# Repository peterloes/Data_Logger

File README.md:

# Next generation of data logger for varied range support of sensors.

A standalone platform to get environmental impact around organisms (animals).
Enable long-term observations of different selectable sensors (I2C Interfaces).
Two pulse counters are included to get lightbarrier activity.

Authors: Loës P., Kempenaers B.(2021) 

## Main advantages against other data logger:

- Available sensors can be freely combined as required.(Firmware adaption)
- Daily regular synchronisation from date and time with DCF77 radio clock receiver.(Firmware adaption)
- Long battery life with lithium battery. (max.17V)
- SD Card includes configuration file.
- Activation times for sensors (x5) to collect data.

## Hardware Design (first draft) supported:

The following firmware is not reviewed.

- Sensirion: Humidity and Temperature Sensor SHT3x-DIS
- Sensirion: CO₂, Humidity and Temperature Sensor SCD30
- Vishay: Fully Integrated Proximity and Ambient Light Sensor with Infrared Emitter VCNL4040
- Pulse Counter     	 

Board Dimensions: 80mm x 60mm

Raw data on SD Card:

https://github.com/peterloes/Data_Logger/blob/main/Getting_Started_Tutorial/4_rawdata_BOX0999.TXT

Configuration data on SD Card:

https://github.com/peterloes/Data_Logger/blob/main/Software/CONFIG.TXT

Schematics:

https://github.com/peterloes/Data_Logger/blob/main/Schematics/Logger.sch.pdf

Housing:

https://github.com/peterloes/Data_Logger/blob/main/Getting_Started_Tutorial/11_Electronic_housing.jpg

## Hyperterminal Screens

Shows SHT31X-D (0x45) and SHT31X-D (0x45)

https://github.com/peterloes/Data_Logger/blob/main/Getting_Started_Tutorial/3_Hyperterminal_3.jpg

https://github.com/peterloes/Data_Logger/blob/main/Getting_Started_Tutorial/3_Hyperterminal_4.jpg

In operation with Interval (configuration.txt) : 3,2V@0,54mA

Shows Vishay VCNL4040 (0x60) and SHT31X-D (0x45)

https://github.com/peterloes/Data_Logger/blob/main/Getting_Started_Tutorial/3_Hyperterminal_5.jpg

Shows Vishay VCNL4040 (0x60) and Sensirion SCD30 CO2 (0x61)

https://github.com/peterloes/Data_Logger/blob/main/Getting_Started_Tutorial/3_Hyperterminal_6.jpg

## Board Power

 - Lithium battery  17V/300mA(maximum) e.g. 12,8V 7,5Ah 96Wh 
 - LS14250 Primary Lithium-Thionyl chloride    3.6V/1200mAh 

Sensors can powered by VBATT_1(3.3V), VBATT_2(3V):

 - Sensirion: Humidity and Temperature Sensor SHT3x-DIS:        600µA@3,3V

 - Sensirion: CO₂, Humidity and Temperature Sensor SCD30:     max.75mA@3,3V 

 - Vishay: Proximity Sensor and Ambient Light Sensor VCNL 4040: 300µA@2,5V

   Similar Software(SensorMon.c): https://github.com/peterloes/HRD_SENSOR

Optional components:

https://github.com/peterloes/Clock_receiver_RFID-MS_MOMO_TAMDL

https://github.com/peterloes/Booter_RFID-MS_MOMO_TAMDL

Outlook:

The Data Logger can feature two arrays with different sensors over 25 meters. (sensor-array x 2)

C is the Greenest Programming Language

To achieve its power and energy-efficiency features, EFM32 products utilize ultralow active and idle power,
fast wakeup and processing times, and most important, the ability to intelligently interact with peripherals
and sensors autonomously without waking up the CPU and consuming more power.

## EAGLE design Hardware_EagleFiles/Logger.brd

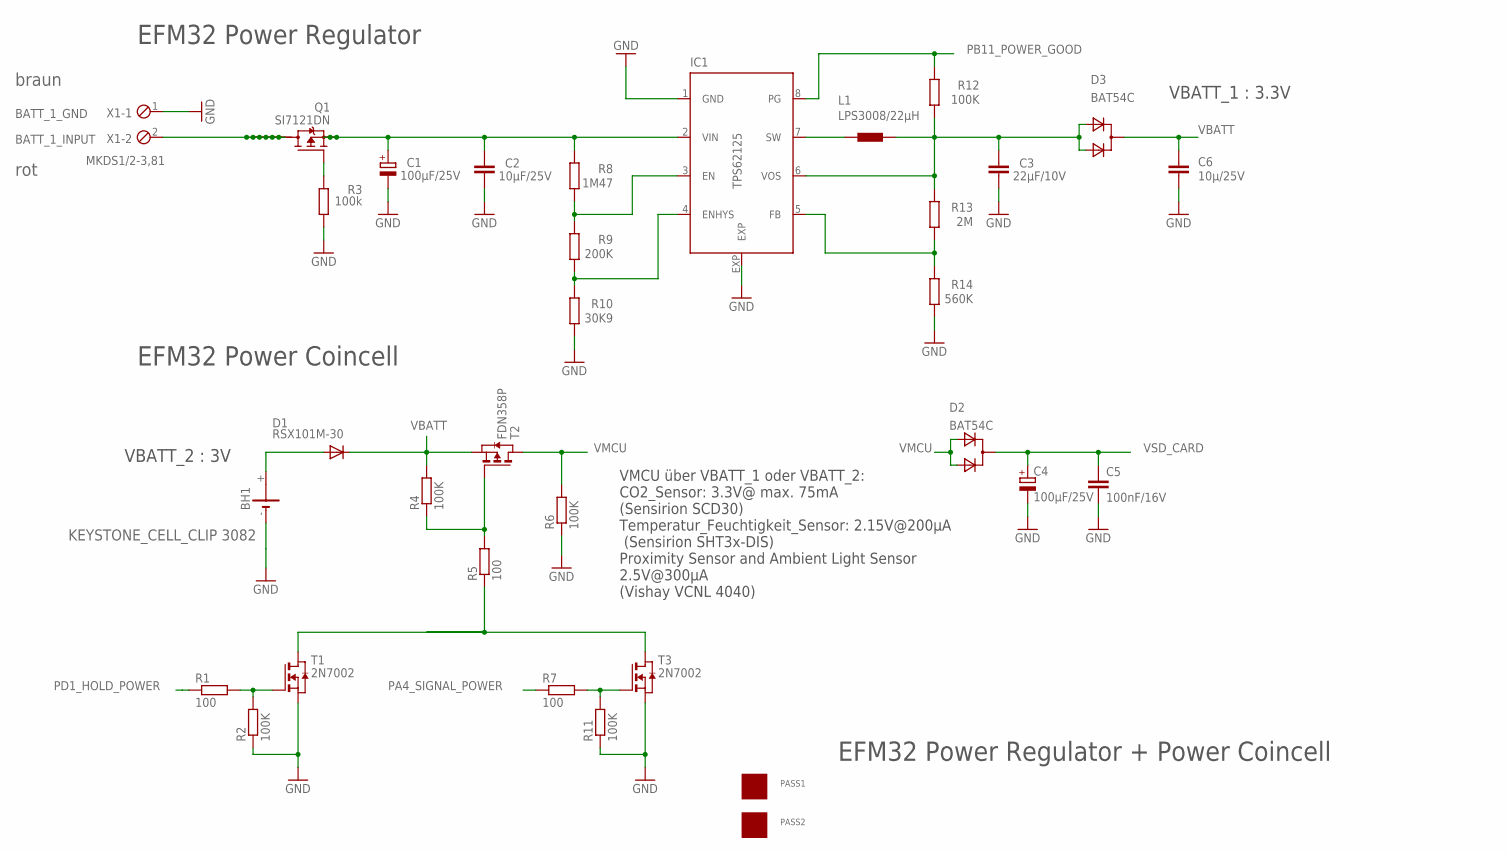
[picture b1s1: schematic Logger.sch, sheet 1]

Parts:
BH1: KEYSTONE_CELL_CLIP 3082; 3082
C1, C4: 100µF/25V; PANASONIC_E
C2: 10µF/25V; C1206
C3: 22µF/10V; C0603
C5: 100nF/16V; C0805
C6: 10µ/25V; C1206
D1: RSX101M-30; SOD123
D2, D3: BAT54C; SOT-23$1
IC1: TPS62125; DSG_PWSO-N8_EXP
L1: LPS3008/22µH; LPS3008
PASS1, PASS2: ROUND_1MM1.5; ROUND2_1.5MM
Q1: SI7121DN; TRANSISTOR-FET_1212-8S
R1, R5, R7: 100; R0805
R2, R4, R6, R11, R12: 100K; R0805
R3: 100k; R0805
R8: 1M47; R0805
R9: 200K; R0805
R10: 30K9; R0805
R13: 2M; R0805
R14: 560K; R0805
T1, T3: 2N7002; SOT-23
T2: FDN358P; ZETEX_SOT-23
X1: MKDS1/2-3,81; 2POL381

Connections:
1: C3.1, D3.2 (A1), D3.3 (A2), IC1.6 (VOS), L1.2, R12.1, R13.2
BATT_INPUT: C1.+, C2.1, IC1.2 (VIN), Q1.1 (S), Q1.2 (S), Q1.3 (S), R8.2
GND: BH1.-, C1.-, C2.2, C3.2, C4.-, C5.2, C6.1, IC1.1 (GND), IC1.EXP, R2.1, R3.1, R6.1, R10.1, R11.1, R14.1, T1.2 (S), T3.2 (S), X1.1; also elsewhere on the board
unnamed: R1.2, R2.2, T1.3 (G)
unnamed: IC1.3 (EN), R8.1, R9.2
unnamed: IC1.4 (ENHYS), R9.1, R10.2
unnamed: IC1.7 (SW), L1.1
unnamed: BH1.+, D1.A
unnamed: Q1.4 (G), R3.2
unnamed: R4.1, R5.2, T2.3 (G)
unnamed: R7.2, R11.2, T3.3 (G)
unnamed: R5.1, T1.1 (D), T3.1 (D)
unnamed: IC1.5 (FB), R13.1, R14.2
PA4_SIGNAL_POWER: R7.1; also elsewhere on the board
PB11_POWER_GOOD: IC1.8 (PG), R12.2; also elsewhere on the board
PD1_HOLD_POWER: R1.1; also elsewhere on the board
VBATT: C6.2, D1.C, D3.1 (C), R4.2, T2.2 (S); also elsewhere on the board
VMCU: D2.2 (A1), D2.3 (A2), R6.2, T2.1 (D); also elsewhere on the board
VSD_CARD: C4.+, C5.1, D2.1 (C); also elsewhere on the board
_: Q1.5 (D), Q1.6 (D), Q1.7 (D), Q1.8 (D), Q1.9 (D), Q1.10 (D), Q1.11 (D), X1.2

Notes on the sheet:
BATT_1_GND
BATT_1_INPUT
EFM32 Power Regulator + Power Coincell
EFM32 Power Regulator
VBATT_1 : 3.3V
braun
rot
EFM32 Power Coincell
VBATT_2 : 3V
VMCU über VBATT_1 oder VBATT_2: CO2_Sensor: 3.3V@ max. 75mA (Sensirion SCD30) Temperatur_Feuchtigkeit_Sensor: 2.15V@200µA (Sensirion SHT3x-DIS) Proximity Sensor and Ambient Light Sensor 2.5V@300µA (Vishay VCNL 4040)

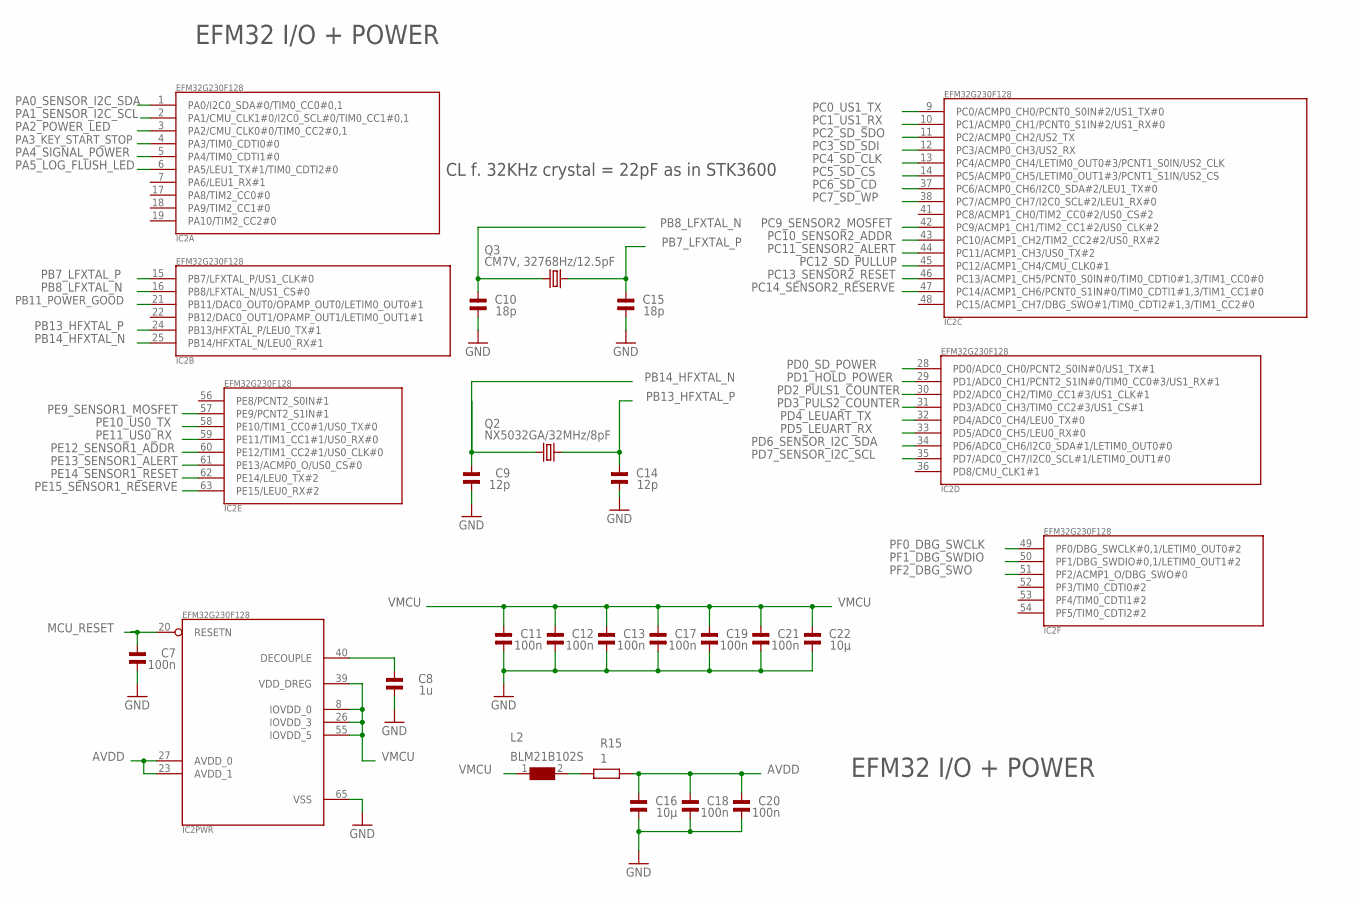
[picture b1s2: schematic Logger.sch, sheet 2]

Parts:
C7, C11, C12, C13, C17, C18, C19, C20, C21: 100n; 0805
C8: 1u; 0805
C9, C14: 12p; 0805
C10, C15: 18p; 0805
C16, C22: 10µ; 0805
IC2: EFM32G230F128; QFN64
L2: BLM21B102S; 0805
Q2: NX5032GA/32MHz/8pF; CRYSTAL2P5.0X3.2
Q3: CM7V, 32768Hz/12.5pF; CRYSTAL2P3.2X1.5
R15: 1; R0805

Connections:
AVDD: C16.2, C18.2, C20.2, IC2.23 (AVDD_1), IC2.27 (AVDD_0), R15.2
GND: C7.1, C8.1, C9.1, C10.1, C11.1, C12.1, C13.1, C14.1, C15.1, C16.1, C17.1, C18.1, C19.1, C20.1, C21.1, C22.1, IC2.65 (VSS); also elsewhere on the board
MCU_RESET: C7.2, IC2.20 (RESETN); also elsewhere on the board
unnamed: L2.2, R15.1
unnamed: C8.2, IC2.40 (DECOUPLE)
PA0_SENSOR_I2C_SDA: IC2.1 (PA0/I2C0_SDA#0/TIM0_CC0#0,1); also elsewhere on the board
PA1_SENSOR_I2C_SCL: IC2.2 (PA1/CMU_CLK1#0/I2C0_SCL#0/TIM0_CC1#0,1); also elsewhere on the board
PA2_POWER_LED: IC2.3 (PA2/CMU_CLK0#0/TIM0_CC2#0,1); also elsewhere on the board
PA3_KEY_START_STOP: IC2.4 (PA3/TIM0_CDTI0#0); also elsewhere on the board
PA4_SIGNAL_POWER: IC2.5 (PA4/TIM0_CDTI1#0); also elsewhere on the board
PA5_LOG_FLUSH_LED: IC2.6 (PA5/LEU1_TX#1/TIM0_CDTI2#0); also elsewhere on the board
PB7_LFXTAL_P: C15.2, IC2.15 (PB7/LFXTAL_P/US1_CLK#0), Q3.2
PB8_LFXTAL_N: C10.2, IC2.16 (PB8/LFXTAL_N/US1_CS#0), Q3.1
PB11_POWER_GOOD: IC2.21 (PB11/DAC0_OUT0/OPAMP_OUT0/LETIM0_OUT0#1); also elsewhere on the board
PB13_HFXTAL_P: C14.2, IC2.24 (PB13/HFXTAL_P/LEU0_TX#1), Q2.2
PB14_HFXTAL_N: C9.2, IC2.25 (PB14/HFXTAL_N/LEU0_RX#1), Q2.1
PC0_US1_TX: IC2.9 (PC0/ACMP0_CH0/PCNT0_S0IN#2/US1_TX#0); also elsewhere on the board
PC1_US1_RX: IC2.10 (PC1/ACMP0_CH1/PCNT0_S1IN#2/US1_RX#0); also elsewhere on the board
PC2_SD_SDO: IC2.11 (PC2/ACMP0_CH2/US2_TX); also elsewhere on the board
PC3_SD_SDI: IC2.12 (PC3/ACMP0_CH3/US2_RX); also elsewhere on the board
PC4_SD_CLK: IC2.13 (PC4/ACMP0_CH4/LETIM0_OUT0#3/PCNT1_S0IN/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); also elsewhere on the board
PC5_SD_CS: IC2.14 (PC5/ACMP0_CH5/LETIM0_OUT1#3/PCNT1_S1IN/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); also elsewhere on the board
PC6_SD_CD: IC2.37 (PC6/ACMP0_CH6/I2C0_SDA#2/LEU1_TX#0); also elsewhere on the board
PC7_SD_WP: IC2.38 (PC7/ACMP0_CH7/I2C0_SCL#2/LEU1_RX#0); also elsewhere on the board
PC9_SENSOR2_MOSFET: IC2.42 (PC9/ACMP1_CH1/TIM2_CC1#2/US0_CLK#2); also elsewhere on the board
PC10_SENSOR2_ADDR: IC2.43 (PC10/ACMP1_CH2/TIM2_CC2#2/US0_RX#2); also elsewhere on the board
PC11_SENSOR2_ALERT: IC2.44 (PC11/ACMP1_CH3/US0_TX#2); also elsewhere on the board
PC12_SD_PULLUP: IC2.45 (PC12/ACMP1_CH4/CMU_CLK0#1); also elsewhere on the board
PC13_SENSOR2_RESET: IC2.46 (PC13/ACMP1_CH5/PCNT0_S0IN#0/TIM0_CDTI0#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); also elsewhere on the board
PC14_SENSOR2_RESERVE: IC2.47 (PC14/ACMP1_CH6/PCNT0_S1IN#0/TIM0_CDTI1#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); also elsewhere on the board
PD0_SD_POWER: IC2.28 (PD0/ADC0_CH0/PCNT2_S0IN#0/US1_TX#1); also elsewhere on the board
PD1_HOLD_POWER: IC2.29 (PD1/ADC0_CH1/PCNT2_S1IN#0/TIM0_CC0#3/US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); also elsewhere on the board
PD2_PULS1_COUNTER: IC2.30 (PD2/ADC0_CH2/TIM0_CC1#3/US1_CLK#1); also elsewhere on the board
PD3_PULS2_COUNTER: IC2.31 (PD3/ADC0_CH3/TIM0_CC2#3/US1_CS#1); also elsewhere on the board
PD4_LEUART_TX: IC2.32 (PD4/ADC0_CH4/LEU0_TX#0); also elsewhere on the board
PD5_LEUART_RX: IC2.33 (PD5/ADC0_CH5/LEU0_RX#0); also elsewhere on the board
PD6_SENSOR_I2C_SDA: IC2.34 (PD6/ADC0_CH6/I2C0_SDA#1/LETIM0_OUT0#0); also elsewhere on the board
PD7_SENSOR_I2C_SCL: IC2.35 (PD7/ADC0_CH7/I2C0_SCL#1/LETIM0_OUT1#0); also elsewhere on the board
PE9_SENSOR1_MOSFET: IC2.57 (PE9/PCNT2_S1IN#1); also elsewhere on the board
PE10_US0_TX: IC2.58 (PE10/TIM1_CC0#1/US0_TX#0); also elsewhere on the board
PE11_US0_RX: IC2.59 (PE11/TIM1_CC1#1/US0_RX#0); also elsewhere on the board
PE12_SENSOR1_ADDR: IC2.60 (PE12/TIM1_CC2#1/US0_CLK#0); also elsewhere on the board
PE13_SENSOR1_ALERT: IC2.61 (PE13/ACMP0_O/US0_CS#0); also elsewhere on the board
PE14_SENSOR1_RESET: IC2.62 (PE14/LEU0_TX#2); also elsewhere on the board
PE15_SENSOR1_RESERVE: IC2.63 (PE15/LEU0_RX#2); also elsewhere on the board
PF0_DBG_SWCLK: IC2.49 (PF0/DBG_SWCLK#0,1/LETIM0_OUT0#2); also elsewhere on the board
PF1_DBG_SWDIO: IC2.50 (PF1/DBG_SWDIO#0,1/LETIM0_OUT1#2); also elsewhere on the board
PF2_DBG_SWO: IC2.51 (PF2/ACMP1_O/DBG_SWO#0); also elsewhere on the board
VMCU: C11.2, C12.2, C13.2, C17.2, C19.2, C21.2, C22.2, IC2.8 (IOVDD_0), IC2.26 (IOVDD_3), IC2.39 (VDD_DREG), IC2.55 (IOVDD_5), L2.1; also elsewhere on the board

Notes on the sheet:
EFM32 I/O + POWER
CL f. 32KHz crystal = 22pF as in STK3600

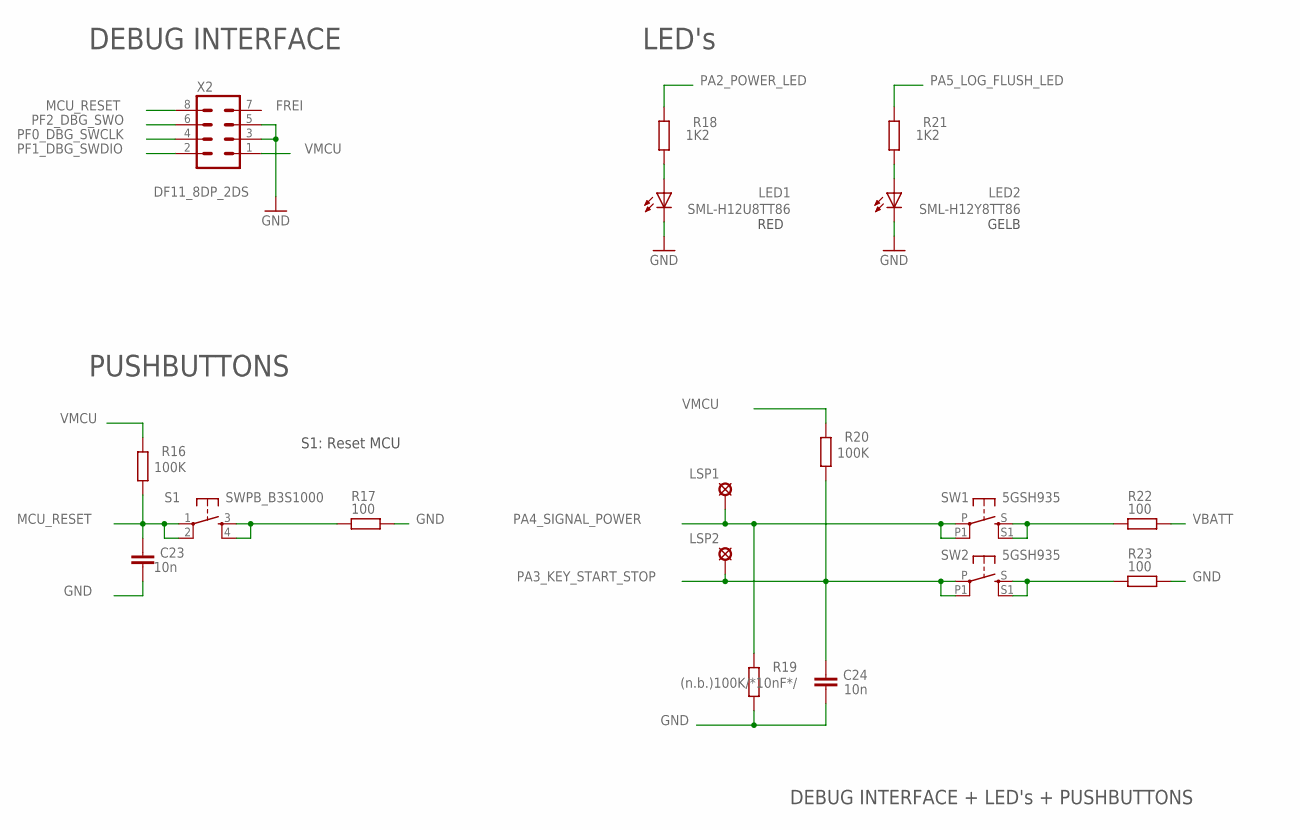
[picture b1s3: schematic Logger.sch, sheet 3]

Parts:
C23: 10n; C0603
C24: 10n; C0603K
LED1: SML-H12U8TT86; CHIPLED_0805
LED2: SML-H12Y8TT86; CHIPLED_0805
LSP1, LSP2: (n.b.)SE13; SE13
R16, R20: 100K; R0805
R17, R22, R23: 100; R0805
R18, R21: 1K2; R0805
R19: (n.b.)100K/*10nF*/; R0805
S1: SWPB_B3S1000; DTSM-6
SW1, SW2: 5GSH935; MULTIMEC_5GSH935
X2: DF11_8DP_2DS; DP11_8DP-2DS

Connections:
GND: C23.1, C24.1, LED1.C, LED2.C, R17.2, R19.1, R23.2, X2.3, X2.5; also elsewhere on the board
MCU_RESET: C23.2, R16.1, S1.1, S1.2, X2.8; also elsewhere on the board
unnamed: LED1.A, R18.2
unnamed: LED2.A, R21.2
unnamed: R17.1, S1.3, S1.4
unnamed: R23.1, SW2.S, SW2.S1
unnamed: R22.1, SW1.S, SW1.S1
PA2_POWER_LED: R18.1; also elsewhere on the board
PA3_KEY_START_STOP: C24.2, LSP2.MP, R20.1, SW2.P, SW2.P1; also elsewhere on the board
PA4_SIGNAL_POWER: LSP1.MP, R19.2, SW1.P, SW1.P1; also elsewhere on the board
PA5_LOG_FLUSH_LED: R21.1; also elsewhere on the board
PF0_DBG_SWCLK: X2.4; also elsewhere on the board
PF1_DBG_SWDIO: X2.2; also elsewhere on the board
PF2_DBG_SWO: X2.6; also elsewhere on the board
VBATT: R22.2; also elsewhere on the board
VMCU: R16.2, R20.2, X2.1; also elsewhere on the board

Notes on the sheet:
DEBUG INTERFACE + LED's + PUSHBUTTONS
DEBUG INTERFACE
LED's
FREI
GELB
PUSHBUTTONS
S1: Reset MCU
RED

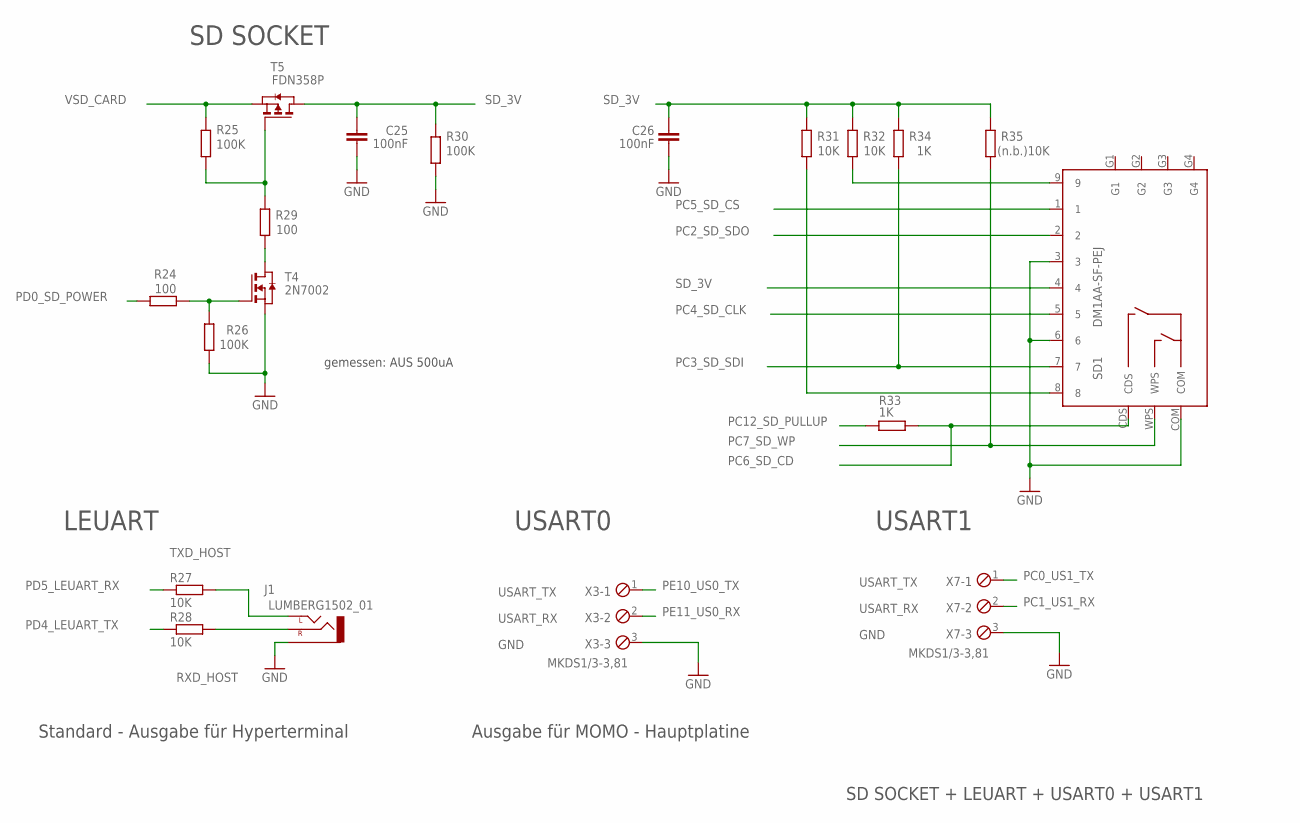
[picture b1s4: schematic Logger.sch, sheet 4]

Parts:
C25, C26: 100nF; C0603
J1: LUMBERG1502_01
R24, R29: 100; R0805
R25, R26, R30: 100K; R0805
R27, R28, R31, R32: 10K; R0805
R33, R34: 1K; R0805
R35: (n.b.)10K; R0805
SD1: DM1AA-SF-PEJ
T4: 2N7002; ZETEX_SOT-23
T5: FDN358P; ZETEX_SOT-23
X3, X7: MKDS1/3-3,81; 3POL381

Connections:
GND: C25.2, C26.2, J1.P$1 (1-SLEEVE), R26.1, R30.1, SD1.3, SD1.6, SD1.COM, T4.2 (S), X3.3, X7.3; also elsewhere on the board
unnamed: R25.1, R29.2, T5.3 (G)
unnamed: R29.1, T4.1 (D)
unnamed: R24.1, R26.2, T4.3 (G)
unnamed: R32.1, SD1.9
unnamed: R31.1, SD1.8
PC0_US1_TX: X7.1; also elsewhere on the board
PC1_US1_RX: X7.2; also elsewhere on the board
PC2_SD_SDO: SD1.2; also elsewhere on the board
PC3_SD_SDI: R34.1, SD1.7; also elsewhere on the board
PC4_SD_CLK: SD1.5; also elsewhere on the board
PC5_SD_CS: SD1.1; also elsewhere on the board
PC6_SD_CD: R33.1, SD1.CDS; also elsewhere on the board
PC7_SD_WP: R35.1, SD1.WPS; also elsewhere on the board
PC12_SD_PULLUP: R33.2; also elsewhere on the board
PD0_SD_POWER: R24.2; also elsewhere on the board
PD4_LEUART_TX: R28.1; also elsewhere on the board
PD5_LEUART_RX: R27.1; also elsewhere on the board
PE10_US0_TX: X3.1; also elsewhere on the board
PE11_US0_RX: X3.2; also elsewhere on the board
RXD_HOST: J1.P$3 (3-RIGHT), R28.2
SD_3V: C25.1, C26.1, R30.2, R31.2, R32.2, R34.2, R35.2, SD1.4, T5.1 (D)
TXD_HOST: J1.P$2 (2-LEFT), R27.2
VSD_CARD: R25.2, T5.2 (S); also elsewhere on the board

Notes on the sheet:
SD SOCKET + LEUART + USART0 + USART1
LEUART
gemessen: AUS 500uA
SD SOCKET
USART_TX
USART_RX
GND
USART0
Standard - Ausgabe für Hyperterminal
Ausgabe für MOMO - Hauptplatine
USART1

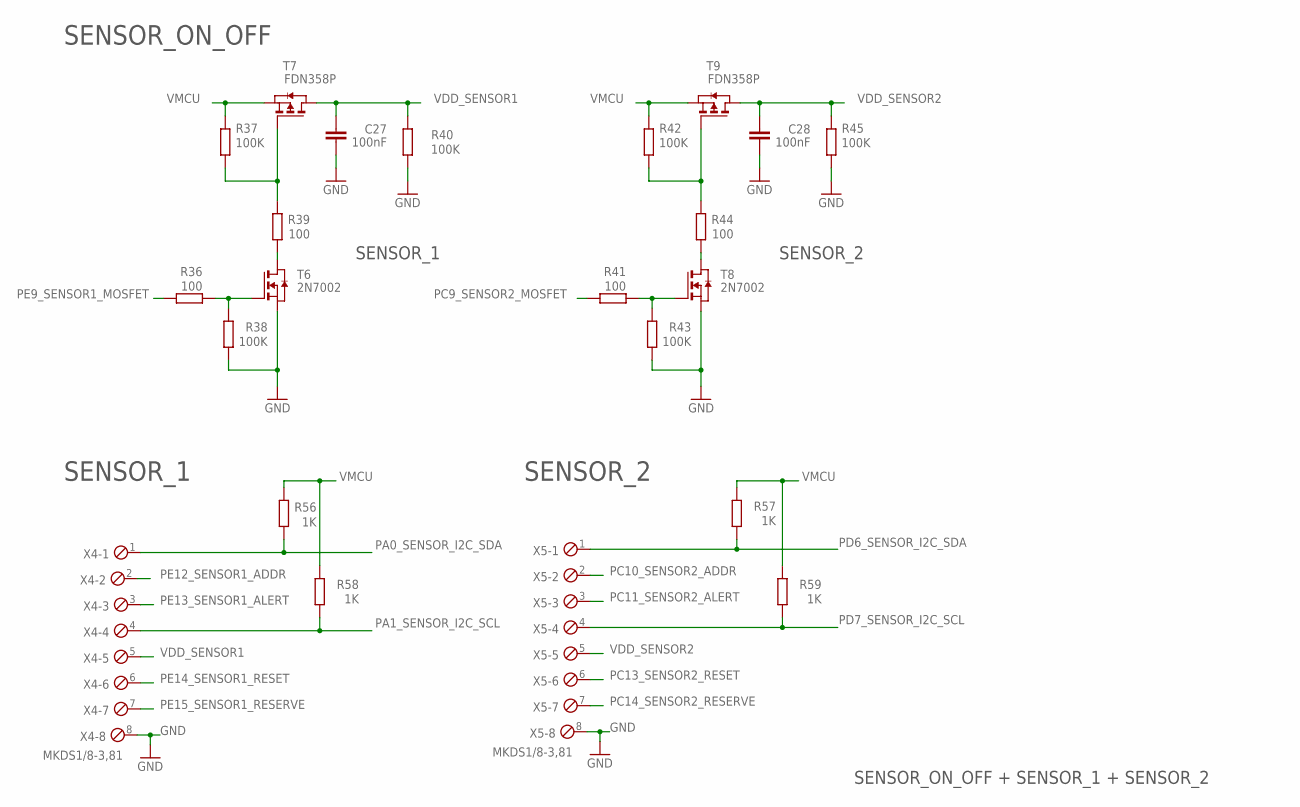
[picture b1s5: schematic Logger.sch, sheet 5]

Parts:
C27, C28: 100nF; C0603
R36, R39, R41, R44: 100; R0805
R37, R38, R40, R42, R43, R45: 100K; R0805
R56, R57, R58, R59: 1K; R0805
T6, T8: 2N7002; ZETEX_SOT-23
T7, T9: FDN358P; ZETEX_SOT-23
X4, X5: MKDS1/8-3,81; 8POL381

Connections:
GND: C27.2, C28.2, R38.1, R40.1, R43.1, R45.1, T6.2 (S), T8.2 (S), X4.8, X5.8; also elsewhere on the board
unnamed: R37.1, R39.2, T7.3 (G)
unnamed: R39.1, T6.1 (D)
unnamed: R36.1, R38.2, T6.3 (G)
unnamed: R42.1, R44.2, T9.3 (G)
unnamed: R44.1, T8.1 (D)
unnamed: R41.1, R43.2, T8.3 (G)
PA0_SENSOR_I2C_SDA: R56.2, X4.1; also elsewhere on the board
PA1_SENSOR_I2C_SCL: R58.1, X4.4; also elsewhere on the board
PC9_SENSOR2_MOSFET: R41.2; also elsewhere on the board
PC10_SENSOR2_ADDR: X5.2; also elsewhere on the board
PC11_SENSOR2_ALERT: X5.3; also elsewhere on the board
PC13_SENSOR2_RESET: X5.6; also elsewhere on the board
PC14_SENSOR2_RESERVE: X5.7; also elsewhere on the board
PD6_SENSOR_I2C_SDA: R57.1, X5.1; also elsewhere on the board
PD7_SENSOR_I2C_SCL: R59.1, X5.4; also elsewhere on the board
PE9_SENSOR1_MOSFET: R36.2; also elsewhere on the board
PE12_SENSOR1_ADDR: X4.2; also elsewhere on the board
PE13_SENSOR1_ALERT: X4.3; also elsewhere on the board
PE14_SENSOR1_RESET: X4.6; also elsewhere on the board
PE15_SENSOR1_RESERVE: X4.7; also elsewhere on the board
VDD_SENSOR1: C27.1, R40.2, T7.1 (D), X4.5
VDD_SENSOR2: C28.1, R45.2, T9.1 (D), X5.5
VMCU: R37.2, R42.2, R56.1, R57.2, R58.2, R59.2, T7.2 (S), T9.2 (S); also elsewhere on the board

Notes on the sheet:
SENSOR_1
SENSOR_2
SENSOR_ON_OFF
SENSOR_ON_OFF + SENSOR_1 + SENSOR_2

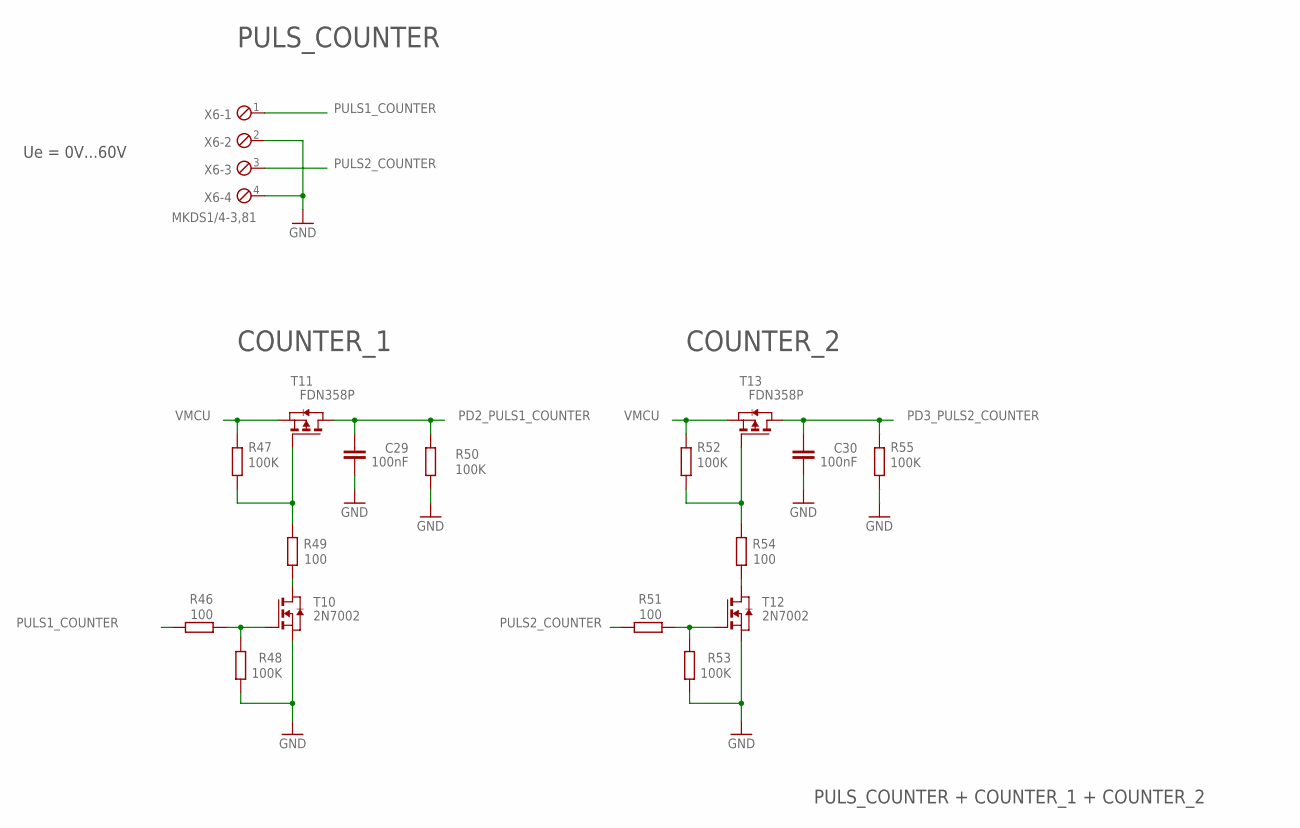
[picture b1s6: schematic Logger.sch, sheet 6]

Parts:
C29, C30: 100nF; C0603
R46, R49, R51, R54: 100; R0805
R47, R48, R50, R52, R53, R55: 100K; R0805
T10, T12: 2N7002; ZETEX_SOT-23
T11, T13: FDN358P; ZETEX_SOT-23
X6: MKDS1/4-3,81; 4POL381

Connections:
GND: C29.2, C30.2, R48.1, R50.1, R53.1, R55.1, T10.2 (S), T12.2 (S), X6.2, X6.4; also elsewhere on the board
unnamed: R47.1, R49.2, T11.3 (G)
unnamed: R49.1, T10.1 (D)
unnamed: R46.1, R48.2, T10.3 (G)
unnamed: R52.1, R54.2, T13.3 (G)
unnamed: R54.1, T12.1 (D)
unnamed: R51.1, R53.2, T12.3 (G)
PD2_PULS1_COUNTER: C29.1, R50.2, T11.1 (D); also elsewhere on the board
PD3_PULS2_COUNTER: C30.1, R55.2, T13.1 (D); also elsewhere on the board
PULS1_COUNTER: R46.2, X6.1
PULS2_COUNTER: R51.2, X6.3
VMCU: R47.2, R52.2, T11.2 (S), T13.2 (S); also elsewhere on the board

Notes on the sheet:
COUNTER_1
COUNTER_2
PULS_COUNTER
PULS_COUNTER + COUNTER_1 + COUNTER_2
Ue = 0V...60V

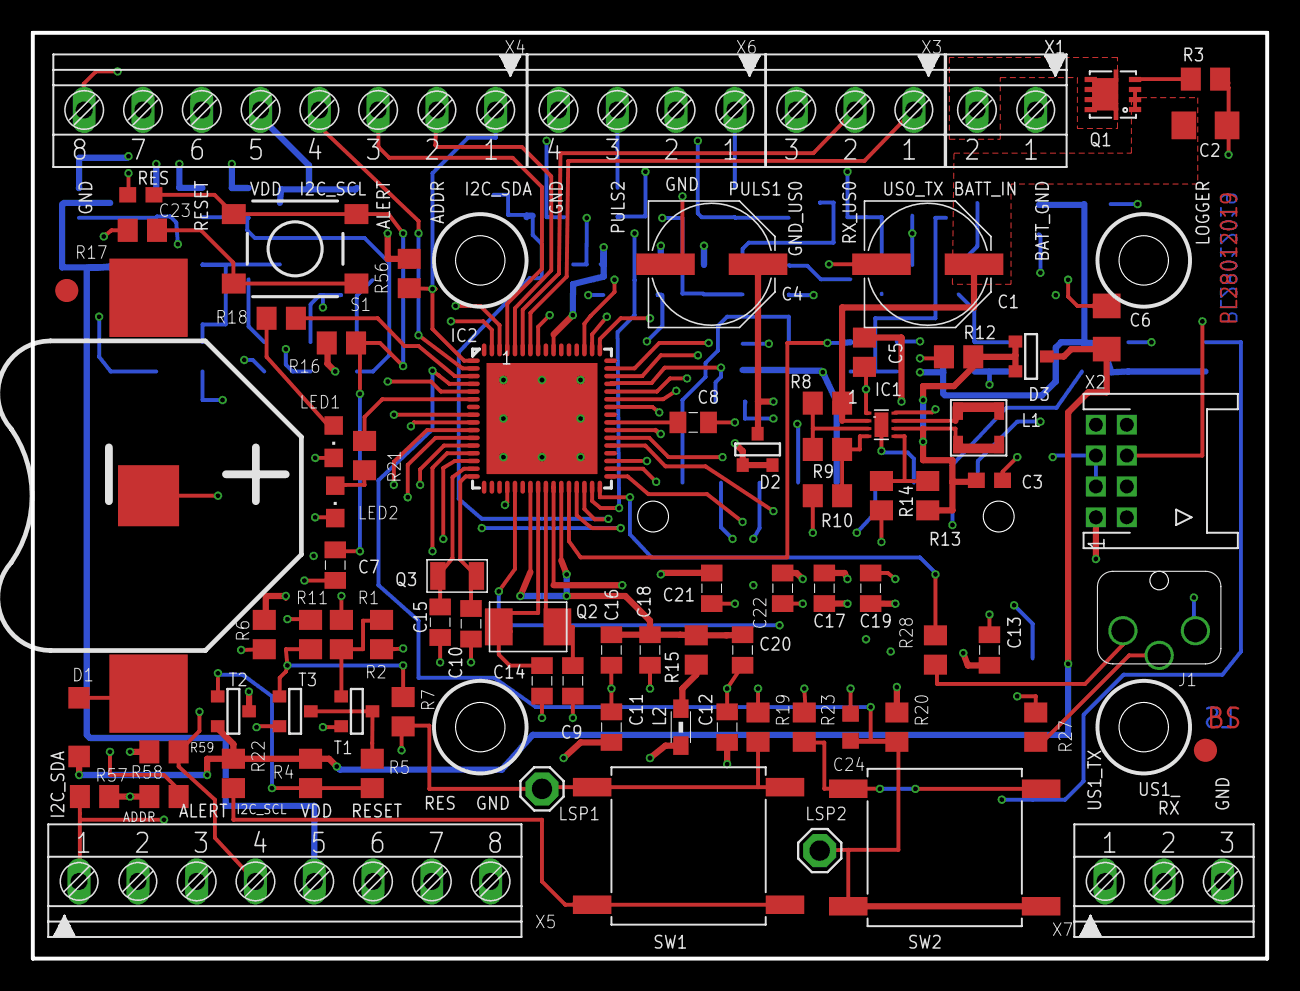
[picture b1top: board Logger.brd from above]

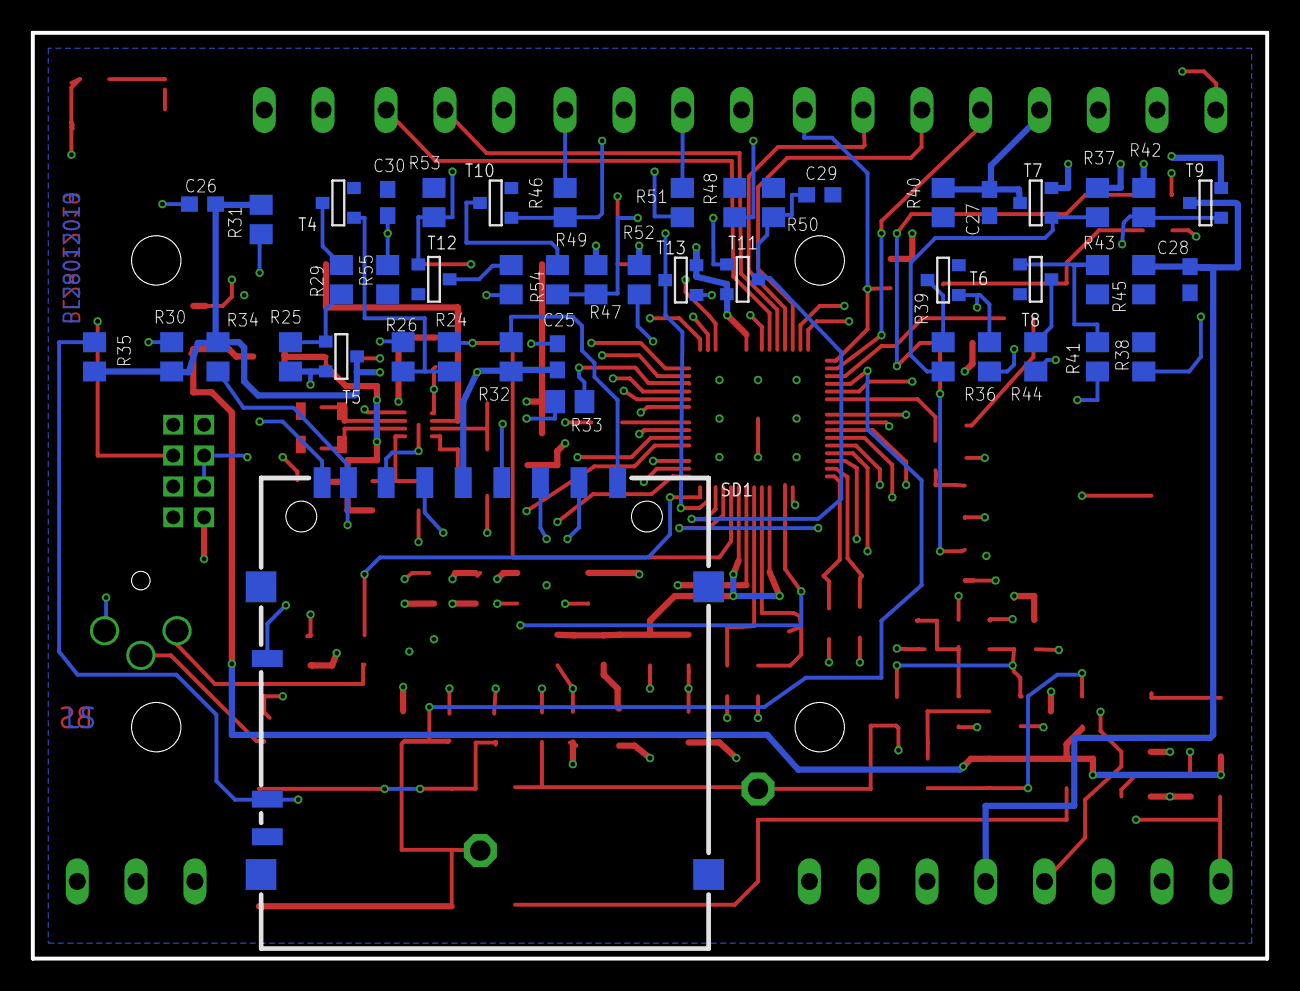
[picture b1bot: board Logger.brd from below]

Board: 4 copper layers, 80.0 x 60.0 mm, 131 parts (47 on the bottom side), 93 nets.

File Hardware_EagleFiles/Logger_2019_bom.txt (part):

Stückliste exportiert aus C:/MPIO/TECHNIK/HARDWARE/EAGLE_FILES/Logger_2019/Logger_2019_1.sch am 21.04.2021 15:29

Part  Value                   Device                  Package                Description                                                    MF MPN     OC_FARNELL OC_NEWARK PACKAGE  SUPPLIER         
BH1   KEYSTONE_CELL_CLIP 3082 3082                    3082                                                                                                                                            
C1    100µF/25V               CPOL-EUE                PANASONIC_E            POLARIZED CAPACITOR, European symbol                                                                                     
C2    10µF/25V                C-EUC1206               C1206                  CAPACITOR, European symbol                                                                                               
C3    22µF/10V                C-EUC0603               C0603                  CAPACITOR, European symbol                                                                                               
C4    100µF/25V               CPOL-EUE                PANASONIC_E            POLARIZED CAPACITOR, European symbol                                                                                     
C5    100nF/16V               C-EUC0805               C0805                  CAPACITOR, European symbol                                                                                               
C6    10µ/25V                 C-EUC1206               C1206                  CAPACITOR, European symbol                                                                                               
C7    100n                    C_SMD0805               0805                                                                                                                                            
C8    1u                      C_SMD0805               0805                                                                                                                                            
C9    12p                     C_SMD0805               0805                                                                                                                                            
C10   18p                     C_SMD0805               0805                                                                                                                                            
C11   100n                    C_SMD0805               0805                                                                                                                                            
C12   100n                    C_SMD0805               0805                                                                                                                                            
C13   100n                    C_SMD0805               0805                                                                                                                                            
C14   12p                     C_SMD0805               0805                                                                                                                                            
C15   18p                     C_SMD0805               0805                                                                                                                                            
C16   10µ                     C_SMD0805               0805                                                                                                                                            
C17   100n                    C_SMD0805               0805                                                                                                                                            
C18   100n                    C_SMD0805               0805                                                                                                                                            
C19   100n                    C_SMD0805               0805                                                                                                                                            
C20   100n                    C_SMD0805               0805                                                                                                                                            
C21   100n                    C_SMD0805               0805                                                                                                                                            
C22   10µ                     C_SMD0805               0805                                                                                                                                            
C23   10n                     C-EUC0603               C0603                  CAPACITOR, European symbol                                                                                               
C24   10n                     C-EUC0603K              C0603K                 CAPACITOR, European symbol                                                                                               
C25   100nF                   C-EUC0603               C0603                  CAPACITOR, European symbol                                                                                               
C26   100nF                   C-EUC0603               C0603                  CAPACITOR, European symbol                                                                                               
C27   100nF                   C-EUC0603               C0603                  CAPACITOR, European symbol                                                                                               
C28   100nF                   C-EUC0603               C0603                  CAPACITOR, European symbol                                                                                               
C29   100nF                   C-EUC0603               C0603                  CAPACITOR, European symbol                                                                                               
C30   100nF                   C-EUC0603               C0603                  CAPACITOR, European symbol                                                                                               
D1    RSX101M-30              DIODE-SOD123            SOD123                 DIODE                                                                                                                    
D2    BAT54C                  D2A_SOT23               SOT-23$1               Dual DIODE                                                                                                               
D3    BAT54C                  D2A_SOT23               SOT-23$1               Dual DIODE                                                                                                               
IC1   TPS62125                TPS62125                DSG_PWSO-N8_EXP                                                                                                                                 
IC2   EFM32G230F128           EFM32G230F128           QFN64                  EFM32G230F128 Gecko Microcontroller in 9mm x 9mm QFN64 package                                                           
J1    LUMBERG1502_01          LUMBERG1502_01          LUMBERG1502_01                                                                                                                                  
L1    LPS3008/22µH            LPS3008                 LPS3008                                                                                                                                         
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

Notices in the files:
parts and their libraries:
EnergyMicro: CC0 License
SparkFun-Aesthetics: Licensing: CC v3.0 Share-Alike You are welcome to use this library for commercial purposes.
